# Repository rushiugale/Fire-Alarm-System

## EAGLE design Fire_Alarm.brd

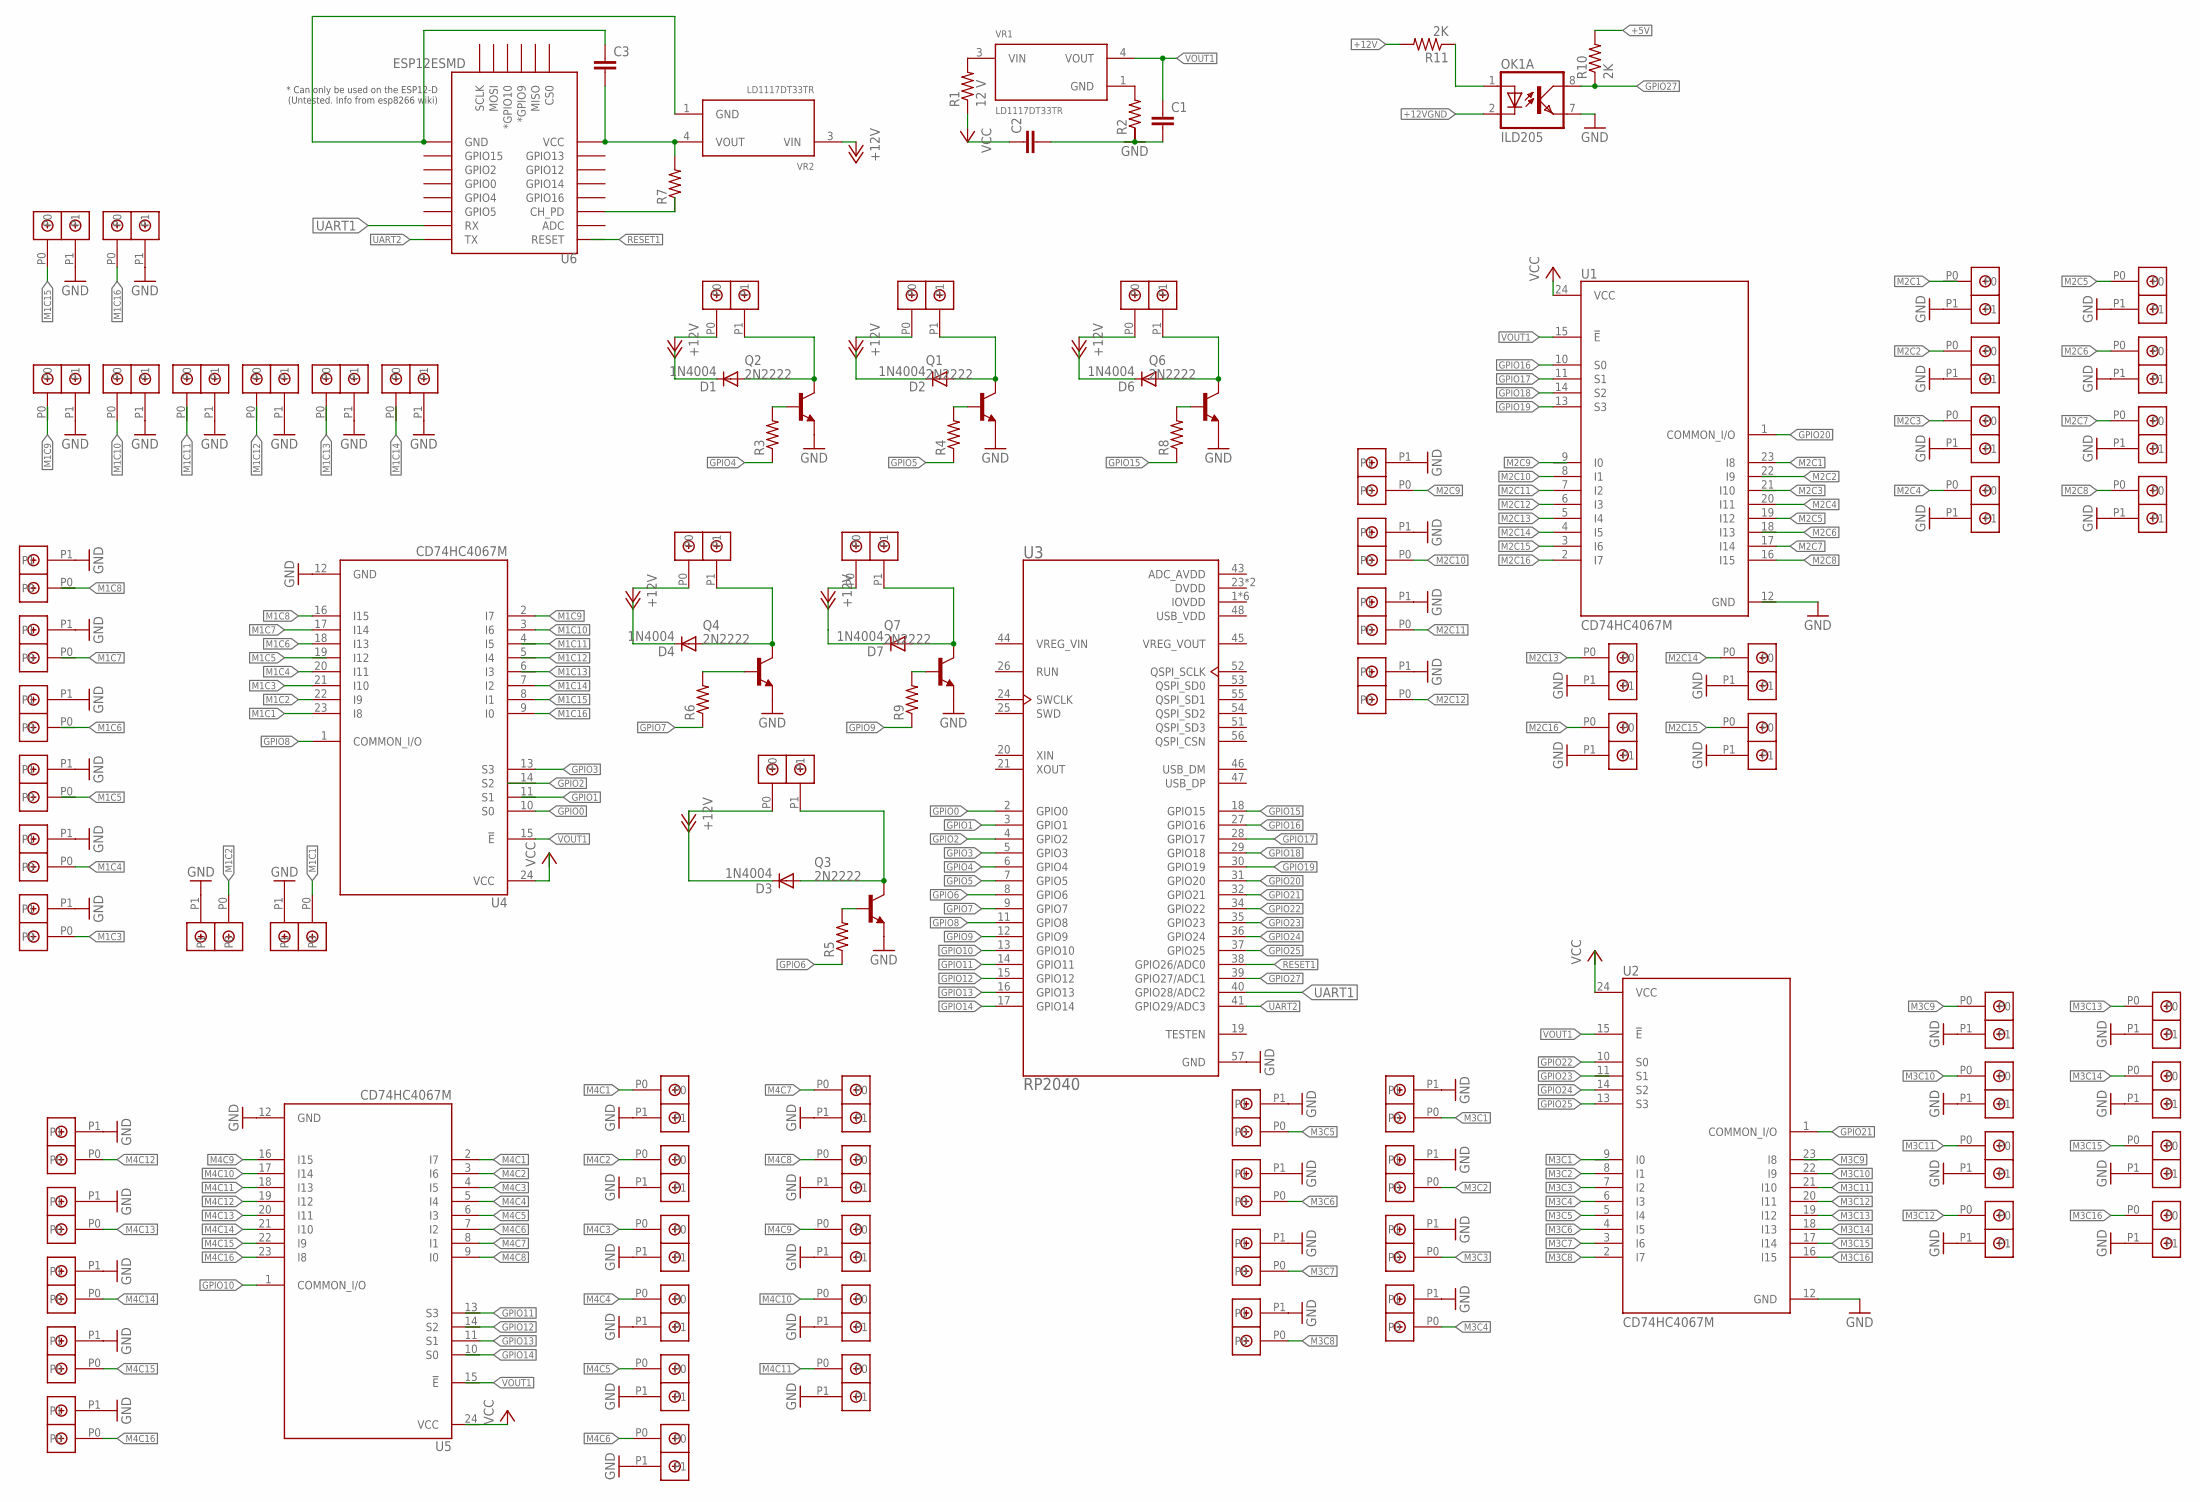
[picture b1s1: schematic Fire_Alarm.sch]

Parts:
C1, C2: C2.5/2; C2.5-2
C3: C5/5.5; C5B5.5
D1, D2, D3, D4, D6, D7: 1N4004; DO41-10
OK1: ILD205; SOIC08
Q1, Q2, Q3, Q4, Q6, Q7: 2N2222; TO18
R1: 12 V; 0204/7
R2: R-US_0204/7; 0204/7
R3, R4, R5, R6, R8, R9: R-US_0204/5; 0204/5
R7: R-US_VTA55; VTA55
R10, R11: 2K; 0204V
U1, U2, U4, U5: CD74HC4067M; SOIC127P1030X265-24N
U3: RP2040; QFN40P700X700X90-57N
U6: ESP12ESMD; ESP12E-SMD
U$1, U$2, U$3, U$4, U$5, U$6, U$7, U$8, U$9, U$10, U$11, U$12, U$13, U$14, U$15, U$16, U$17, U$18, U$19, U$20, U$21, U$22, U$23, U$24, U$25, U$26, U$27, U$28, U$29, U$30, U$31, U$32, U$33, U$34, U$35, U$36, U$37, U$38, U$39, U$40, U$41, U$42, U$43, U$44, U$45, U$47, U$48, U$49, U$50, U$51, U$52, U$54, U$55, U$57, U$58, U$59, U$60, U$61, U$62, U$63, U$64, U$65, U$66, U$67, U$68, U$69, U$70, U$71, U$72, U$73: DBCONN-1X2
VR1, VR2: LD1117DT33TR; DPAK456P1010X240-3N

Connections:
+5V: R10.2
+12V: R11.2, U$57.P0, U$58.P0, U$69.P0, U$70.P0, U$71.P0, U$72.P0, VR2.3 (VIN)
+12VGND: OK1.2 (C)
ADC_AVDD: U3.43 (ADC_AVDD)
DVDD: U3.23 (DVDD), U3.50 (DVDD)
GND: OK1.7 (EMIT), Q1.1 (E), Q2.1 (E), Q3.1 (E), Q4.1 (E), Q6.1 (E), Q7.1 (E), U1.12 (GND), U2.12 (GND), U3.57 (GND), U4.12 (GND), U5.12 (GND), U$1.P1, U$2.P1, U$3.P1, U$4.P1, U$5.P1, U$6.P1, U$7.P1, U$8.P1, U$9.P1, U$10.P1, U$11.P1, U$12.P1, U$13.P1, U$14.P1, U$15.P1, U$16.P1, U$17.P1, U$18.P1, U$19.P1, U$20.P1, U$21.P1, U$22.P1, U$23.P1, U$24.P1, U$25.P1, U$26.P1, U$27.P1, U$28.P1, U$29.P1, U$30.P1, U$31.P1, U$32.P1, U$33.P1, U$34.P1, U$35.P1, U$36.P1, U$37.P1, U$38.P1, U$39.P1, U$40.P1, U$41.P1, U$42.P1, U$43.P1, U$44.P1, U$45.P1, U$47.P1, U$48.P1, U$49.P1, U$50.P1, U$51.P1, U$52.P1, U$54.P1, U$55.P1, U$59.P1, U$60.P1, U$61.P1, U$62.P1, U$63.P1, U$64.P1, U$65.P1, U$66.P1, U$67.P1, U$68.P1, U$73.P1
GPIO0: U3.2 (GPIO0), U4.10 (S0)
GPIO1: U3.3 (GPIO1)
GPIO2: U3.4 (GPIO2)
GPIO3: U3.5 (GPIO3), U4.13 (S3)
GPIO4: R3.1, U3.6 (GPIO4)
GPIO5: R4.1, U3.7 (GPIO5)
GPIO6: R5.1, U3.8 (GPIO6)
GPIO7: R6.1, U3.9 (GPIO7)
GPIO8: U3.11 (GPIO8), U4.1 (COMMON_I/O)
GPIO9: R9.1, U3.12 (GPIO9)
GPIO10: U3.13 (GPIO10), U5.1 (COMMON_I/O)
GPIO11: U3.14 (GPIO11)
GPIO12: U3.15 (GPIO12)
GPIO13: U3.16 (GPIO13), U5.11 (S1)
GPIO14: U3.17 (GPIO14)
GPIO15: R8.1, U3.18 (GPIO15)
GPIO16: U1.10 (S0), U3.27 (GPIO16)
GPIO17: U1.11 (S1), U3.28 (GPIO17)
GPIO18: U1.14 (S2), U3.29 (GPIO18)
GPIO19: U1.13 (S3), U3.30 (GPIO19)
GPIO20: U1.1 (COMMON_I/O), U3.31 (GPIO20)
GPIO21: U2.1 (COMMON_I/O), U3.32 (GPIO21)
GPIO22: U2.10 (S0), U3.34 (GPIO22)
GPIO23: U3.35 (GPIO23)
GPIO24: U2.14 (S2), U3.36 (GPIO24)
GPIO25: U2.13 (S3), U3.37 (GPIO25)
GPIO27: OK1.8 (COL), R10.1, U3.39 (GPIO27/ADC1)
IOVDD: U3.1 (IOVDD), U3.10 (IOVDD), U3.22 (IOVDD), U3.33 (IOVDD), U3.42 (IOVDD), U3.49 (IOVDD)
M1C1: U4.23 (I8), U$19.P0
M1C2: U4.22 (I9), U$17.P0
M1C3: U4.21 (I10), U$20.P0
M1C4: U4.20 (I11), U$18.P0
M1C6: U4.18 (I13)
M1C7: U4.17 (I14)
M1C8: U4.16 (I15)
M1C9: U4.2 (I7)
M1C10: U4.3 (I6)
M1C14: U4.7 (I2)
M1C15: U4.8 (I1), U$3.P0
M1C16: U4.9 (I0), U$2.P0
M2C1: U1.23 (I8)
M2C4: U1.20 (I11), U$23.P0
M2C5: U1.19 (I12), U$28.P0
M2C6: U$24.P0
M2C7: U1.17 (I14)
M2C8: U1.16 (I15)
M2C9: U$38.P0
M2C10: U1.8 (I1), U$39.P0
M2C11: U1.7 (I2), U$37.P0
M2C12: U1.6 (I3), U$41.P0
M2C13: U1.5 (I4), U$40.P0
M2C14: U1.4 (I5), U$44.P0
M2C15: U1.3 (I6), U$43.P0
M2C16: U1.2 (I7), U$42.P0
M3C1: U$33.P0
M3C2: U2.8 (I1), U$36.P0
M3C3: U2.7 (I2), U$35.P0
M3C4: U2.6 (I3), U$32.P0
M3C5: U2.5 (I4), U$4.P0
M3C6: U2.4 (I5), U$5.P0
M3C7: U2.3 (I6), U$30.P0
M3C8: U2.2 (I7), U$31.P0
M3C9: U$63.P0
M3C10: U2.22 (I9), U$65.P0
M3C11: U2.21 (I10), U$67.P0
M3C12: U2.20 (I11), U$68.P0
M3C13: U2.19 (I12), U$61.P0
M3C14: U2.18 (I13), U$62.P0
M3C15: U2.17 (I14), U$64.P0
M3C16: U2.16 (I15), U$66.P0
M4C1: U5.2 (I7), U$47.P0
M4C2: U5.3 (I6), U$45.P0
M4C3: U5.4 (I5), U$29.P0
M4C4: U5.5 (I4), U$52.P0
M4C5: U5.6 (I3), U$34.P0
M4C6: U5.7 (I2), U$73.P0
M4C7: U5.8 (I1), U$51.P0
M4C8: U5.9 (I0), U$59.P0
M4C9: U5.16 (I15), U$25.P0
M4C10: U5.17 (I14), U$26.P0
M4C11: U5.18 (I13), U$50.P0
M4C12: U5.19 (I12), U$49.P0
M4C13: U5.20 (I11), U$48.P0
M4C14: U5.21 (I10), U$54.P0
M4C15: U5.22 (I9), U$60.P0
M4C16: U5.23 (I8), U$55.P0
unnamed: OK1.1 (A), R11.1
unnamed: R1.2, VR1.3 (VIN)
unnamed: R2.2, VR1.1 (GND)
unnamed: C1.2, C2.2, R2.1
unnamed: D1.A, Q2.3 (C), U$71.P1
unnamed: Q2.2 (B), R3.2
unnamed: Q1.2 (B), R4.2
unnamed: D2.A, Q1.3 (C), U$58.P1
unnamed: Q3.2 (B), R5.2
unnamed: D3.A, Q3.3 (C), U$70.P1
unnamed: Q4.2 (B), R6.2
unnamed: D4.A, Q4.3 (C), U$57.P1
unnamed: C3.2, R7.2, U6.VCC, VR2.4 (VOUT)
unnamed: C3.1, U6.GND, VR2.1 (GND)
unnamed: Q6.2 (B), R8.2
unnamed: D6.A, Q6.3 (C), U$69.P1
unnamed: Q7.2 (B), R9.2
unnamed: D7.A, Q7.3 (C), U$72.P1
RESET1: U3.38 (GPIO26/ADC0)
UART1: U3.40 (GPIO28/ADC2), U6.RXD0 (RX)
UART2: U3.41 (GPIO29/ADC3), U6.TXD0 (TX)
USB_VDD: U3.48 (USB_VDD)
VCC: R1.1, U1.24 (VCC), U5.24 (VCC)
VOUT1: C1.1, U1.15 (!E), U2.15 (!E), U4.15 (!E), VR1.4 (VOUT)

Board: 2 copper layers, 105 parts (0 on the bottom side), 92 nets, no tracks yet.
